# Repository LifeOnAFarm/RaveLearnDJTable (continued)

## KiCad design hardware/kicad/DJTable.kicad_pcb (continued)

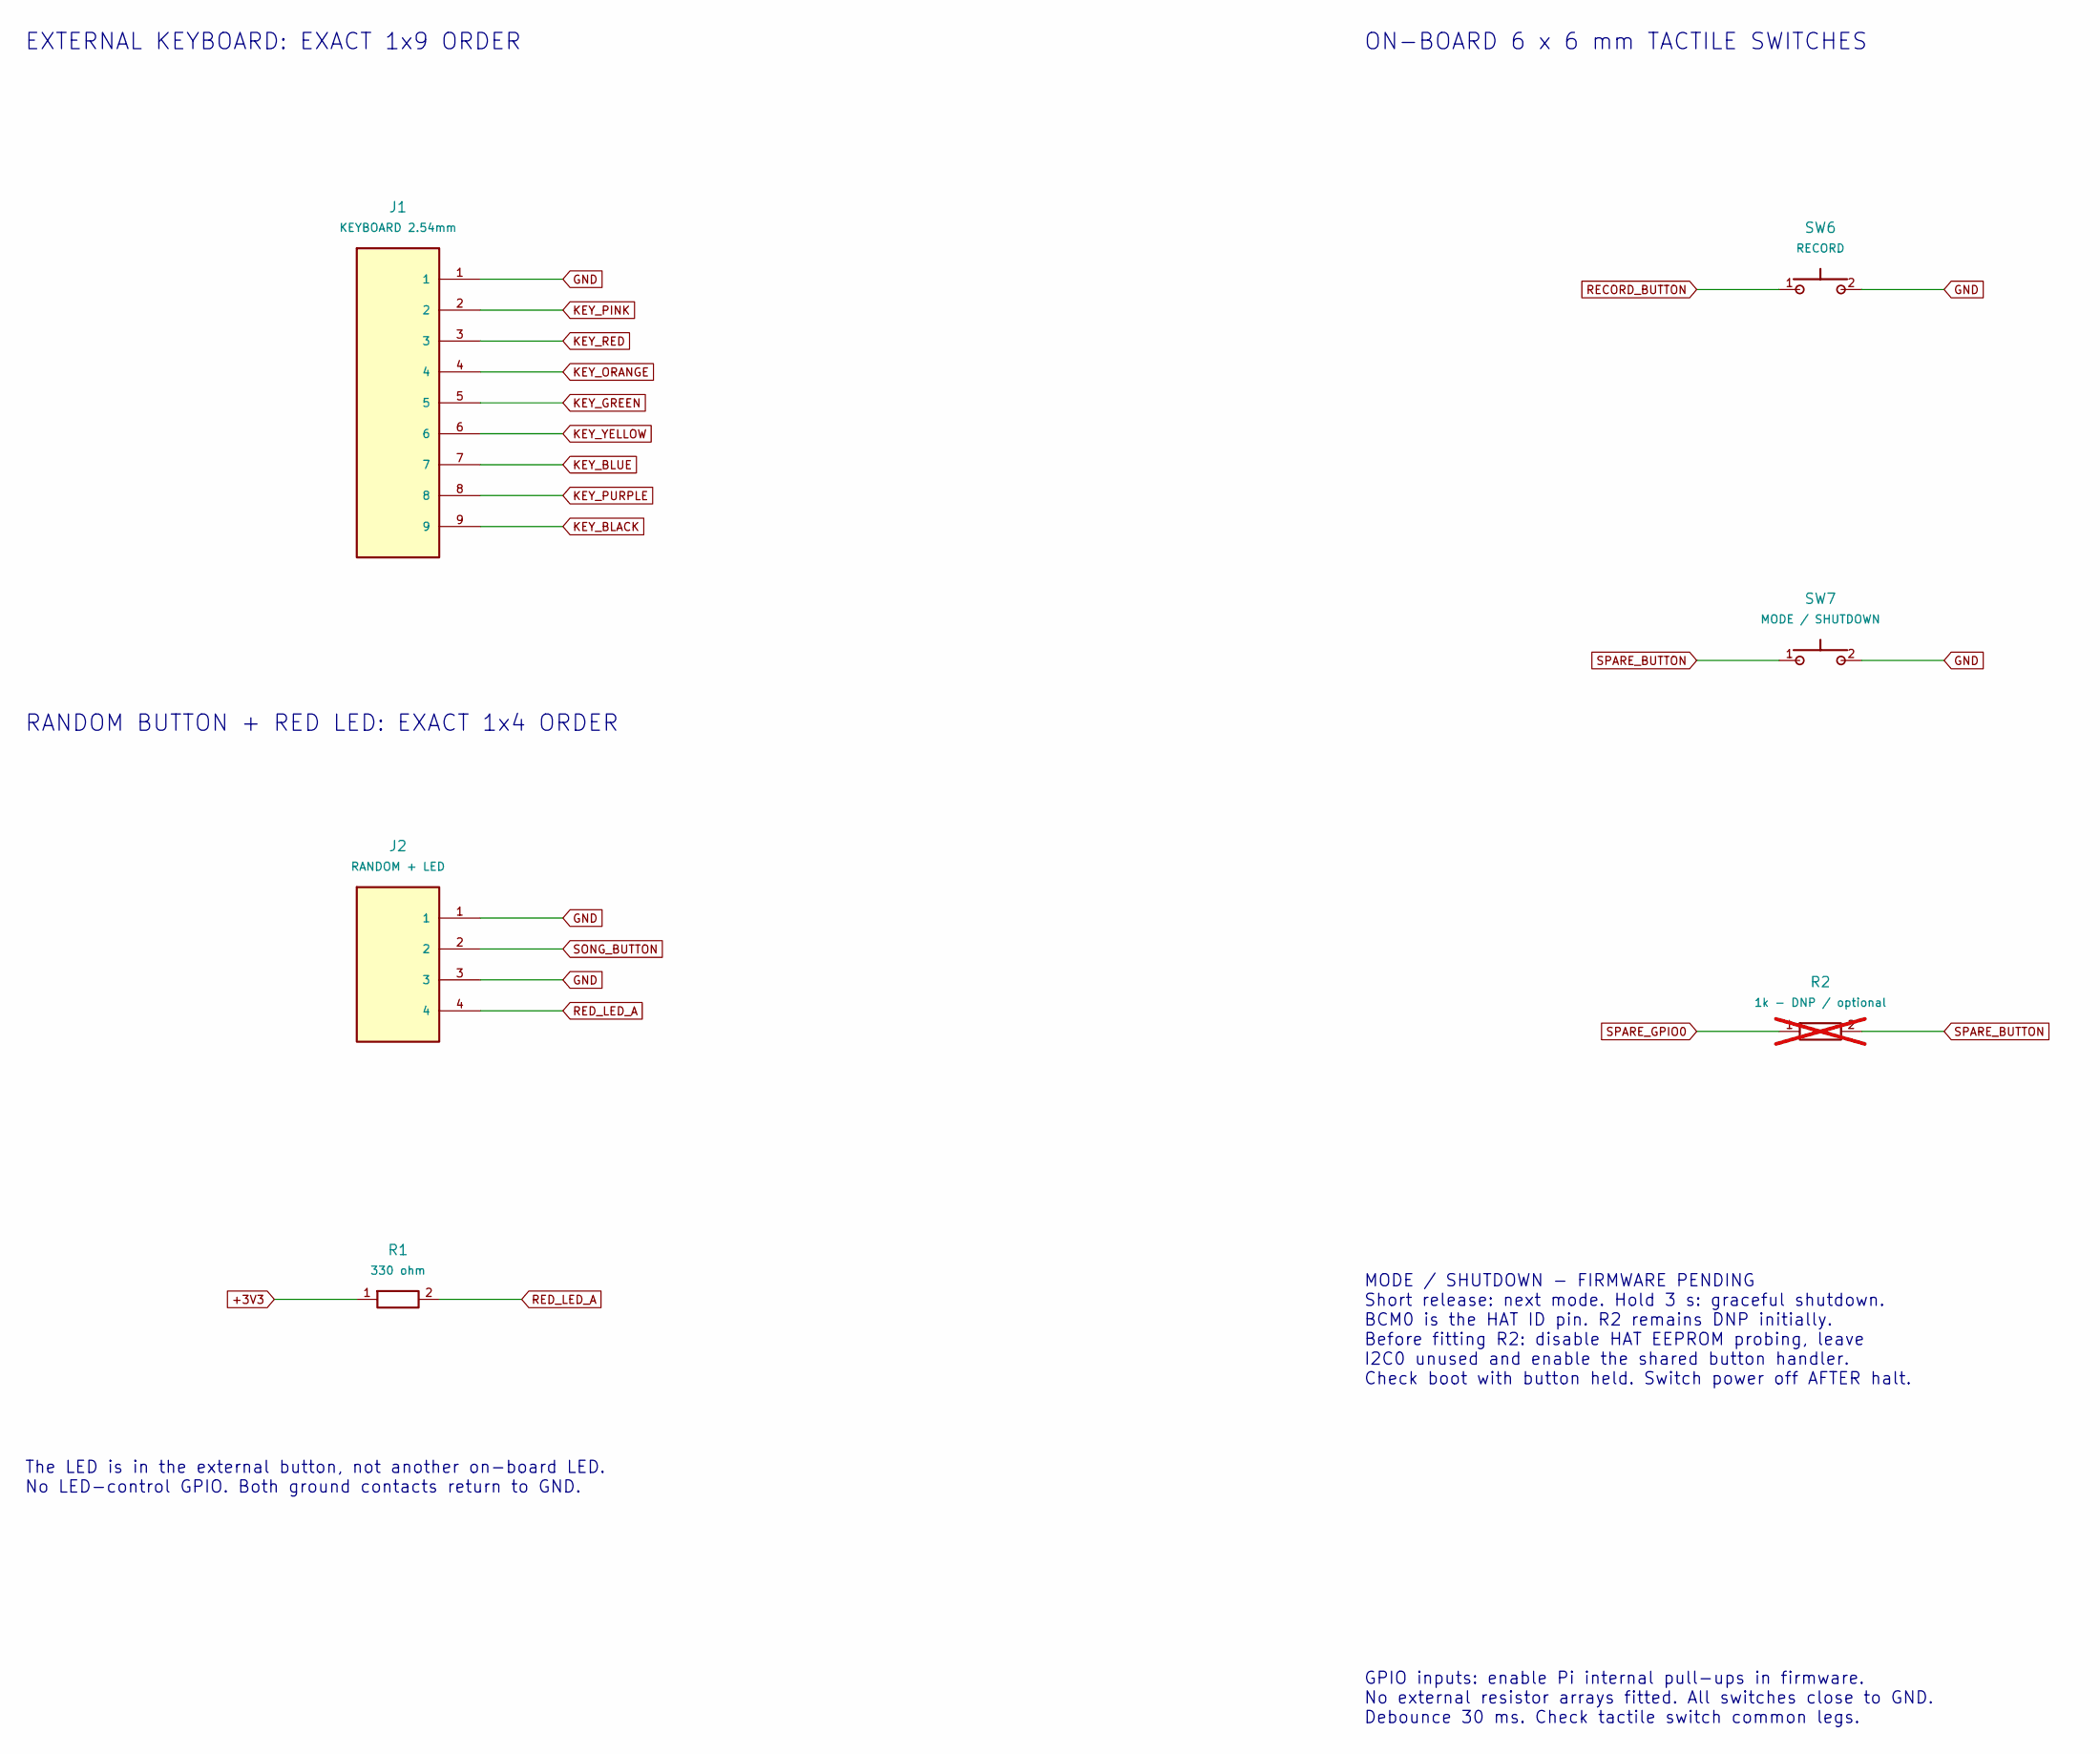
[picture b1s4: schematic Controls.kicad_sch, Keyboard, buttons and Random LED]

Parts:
J1: KEYBOARD 2.54mm; PinHeader_1x09_P2.54mm_Vertical
J2: RANDOM + LED; PinHeader_1x04_P2.54mm_Vertical
R1: 330 ohm; R_1206_3216Metric_Pad1.30x1.75mm_HandSolder
R2: 1k - DNP / optional; R_1206_3216Metric_Pad1.30x1.75mm_HandSolder; not fitted
SW6: RECORD; SW_PUSH_6mm
SW7: MODE / SHUTDOWN; SW_PUSH_6mm

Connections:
+3V3: R1.1; also elsewhere on the board
GND: J1.1, J2.1, J2.3, SW6.2, SW7.2; also elsewhere on the board
KEY_BLACK: J1.9; also elsewhere on the board
KEY_BLUE: J1.7; also elsewhere on the board
KEY_GREEN: J1.5; also elsewhere on the board
KEY_ORANGE: J1.4; also elsewhere on the board
KEY_PINK: J1.2; also elsewhere on the board
KEY_PURPLE: J1.8; also elsewhere on the board
KEY_RED: J1.3; also elsewhere on the board
KEY_YELLOW: J1.6; also elsewhere on the board
RECORD_BUTTON: SW6.1; also elsewhere on the board
RED_LED_A: J2.4, R1.2
SONG_BUTTON: J2.2; also elsewhere on the board
SPARE_BUTTON: R2.2, SW7.1
SPARE_GPIO0: R2.1; also elsewhere on the board

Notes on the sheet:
GPIO inputs: enable Pi internal pull-ups in firmware. No external resistor arrays fitted. All switches close to GND. Debounce 30 ms. Check tactile switch common legs.
EXTERNAL KEYBOARD: EXACT 1x9 ORDER
MODE / SHUTDOWN - FIRMWARE PENDING Short release: next mode. Hold 3 s: graceful shutdown. BCM0 is the HAT ID pin. R2 remains DNP initially. Before fitting R2: disable HAT EEPROM probing, leave I2C0 unused and enable the shared button handler. Check boot with button held. Switch power off AFTER halt.
ON-BOARD 6 x 6 mm TACTILE SWITCHES
RANDOM BUTTON + RED LED: EXACT 1x4 ORDER
The LED is in the external button, not another on-board LED. No LED-control GPIO. Both ground contacts return to GND.

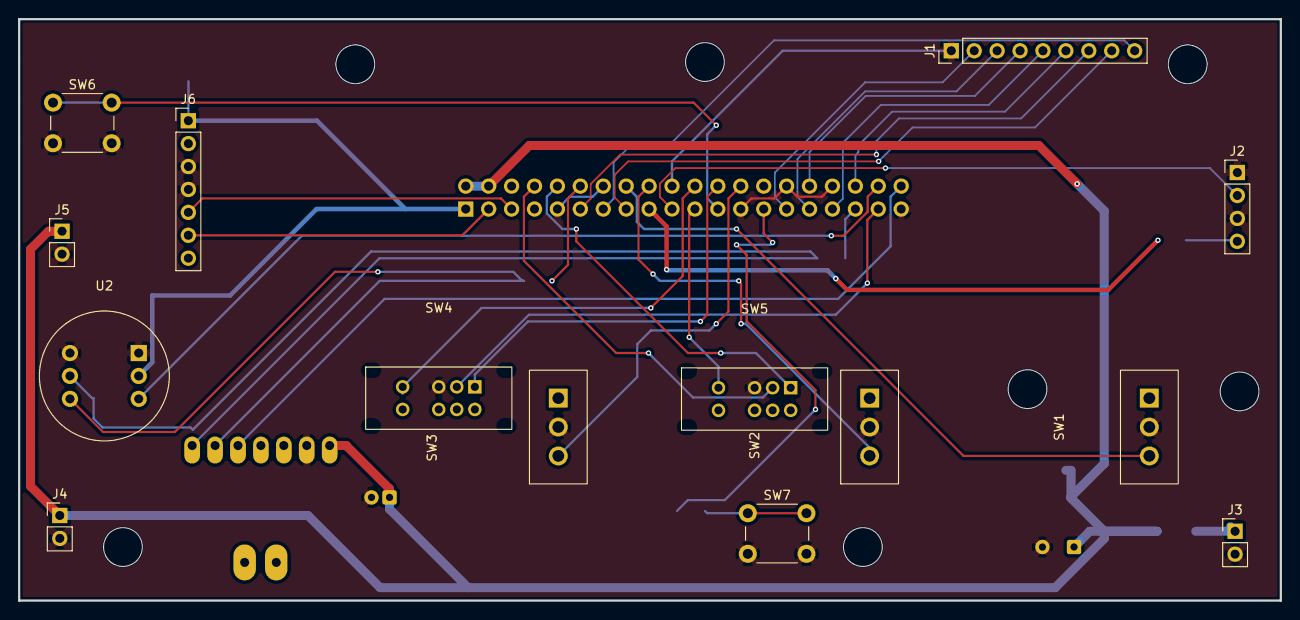
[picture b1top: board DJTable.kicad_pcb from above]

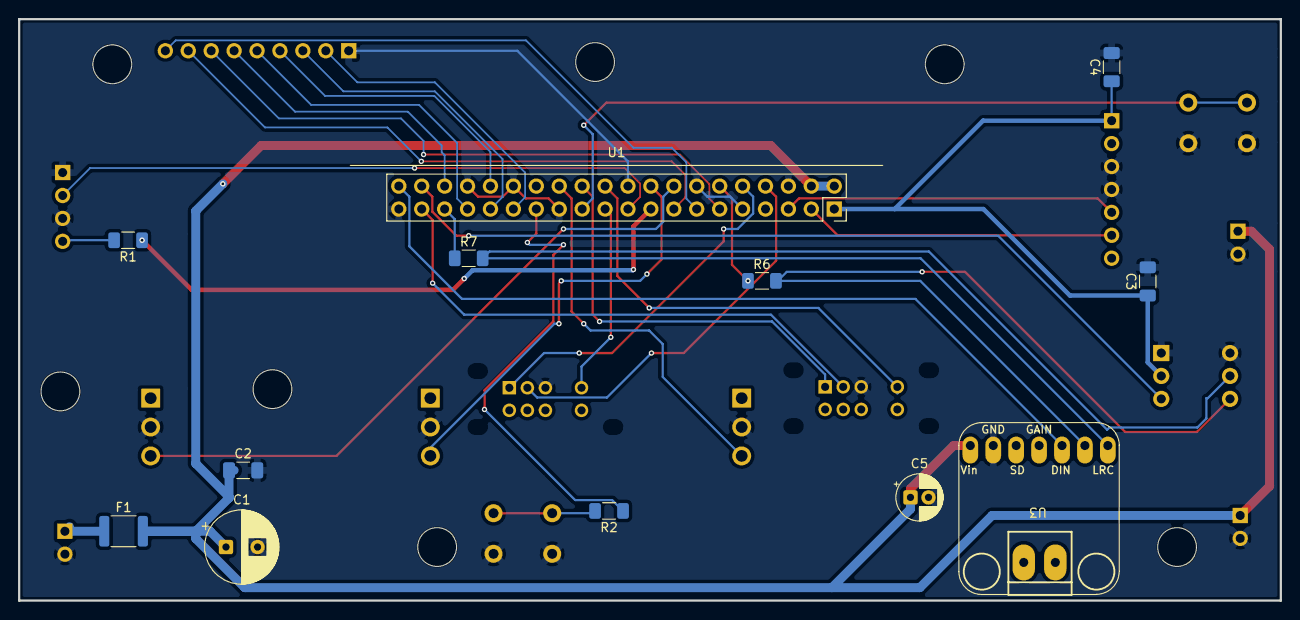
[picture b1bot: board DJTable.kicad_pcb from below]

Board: 2 copper layers, 139.8 x 64.4 mm, 26 parts (12 on the bottom side), 34 nets.

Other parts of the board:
C3: 100nF; C_1206_3216Metric_Pad1.33x1.80mm_HandSolder

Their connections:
+3V3: C3.1; also elsewhere on the board
GND: C3.2; also elsewhere on the board
